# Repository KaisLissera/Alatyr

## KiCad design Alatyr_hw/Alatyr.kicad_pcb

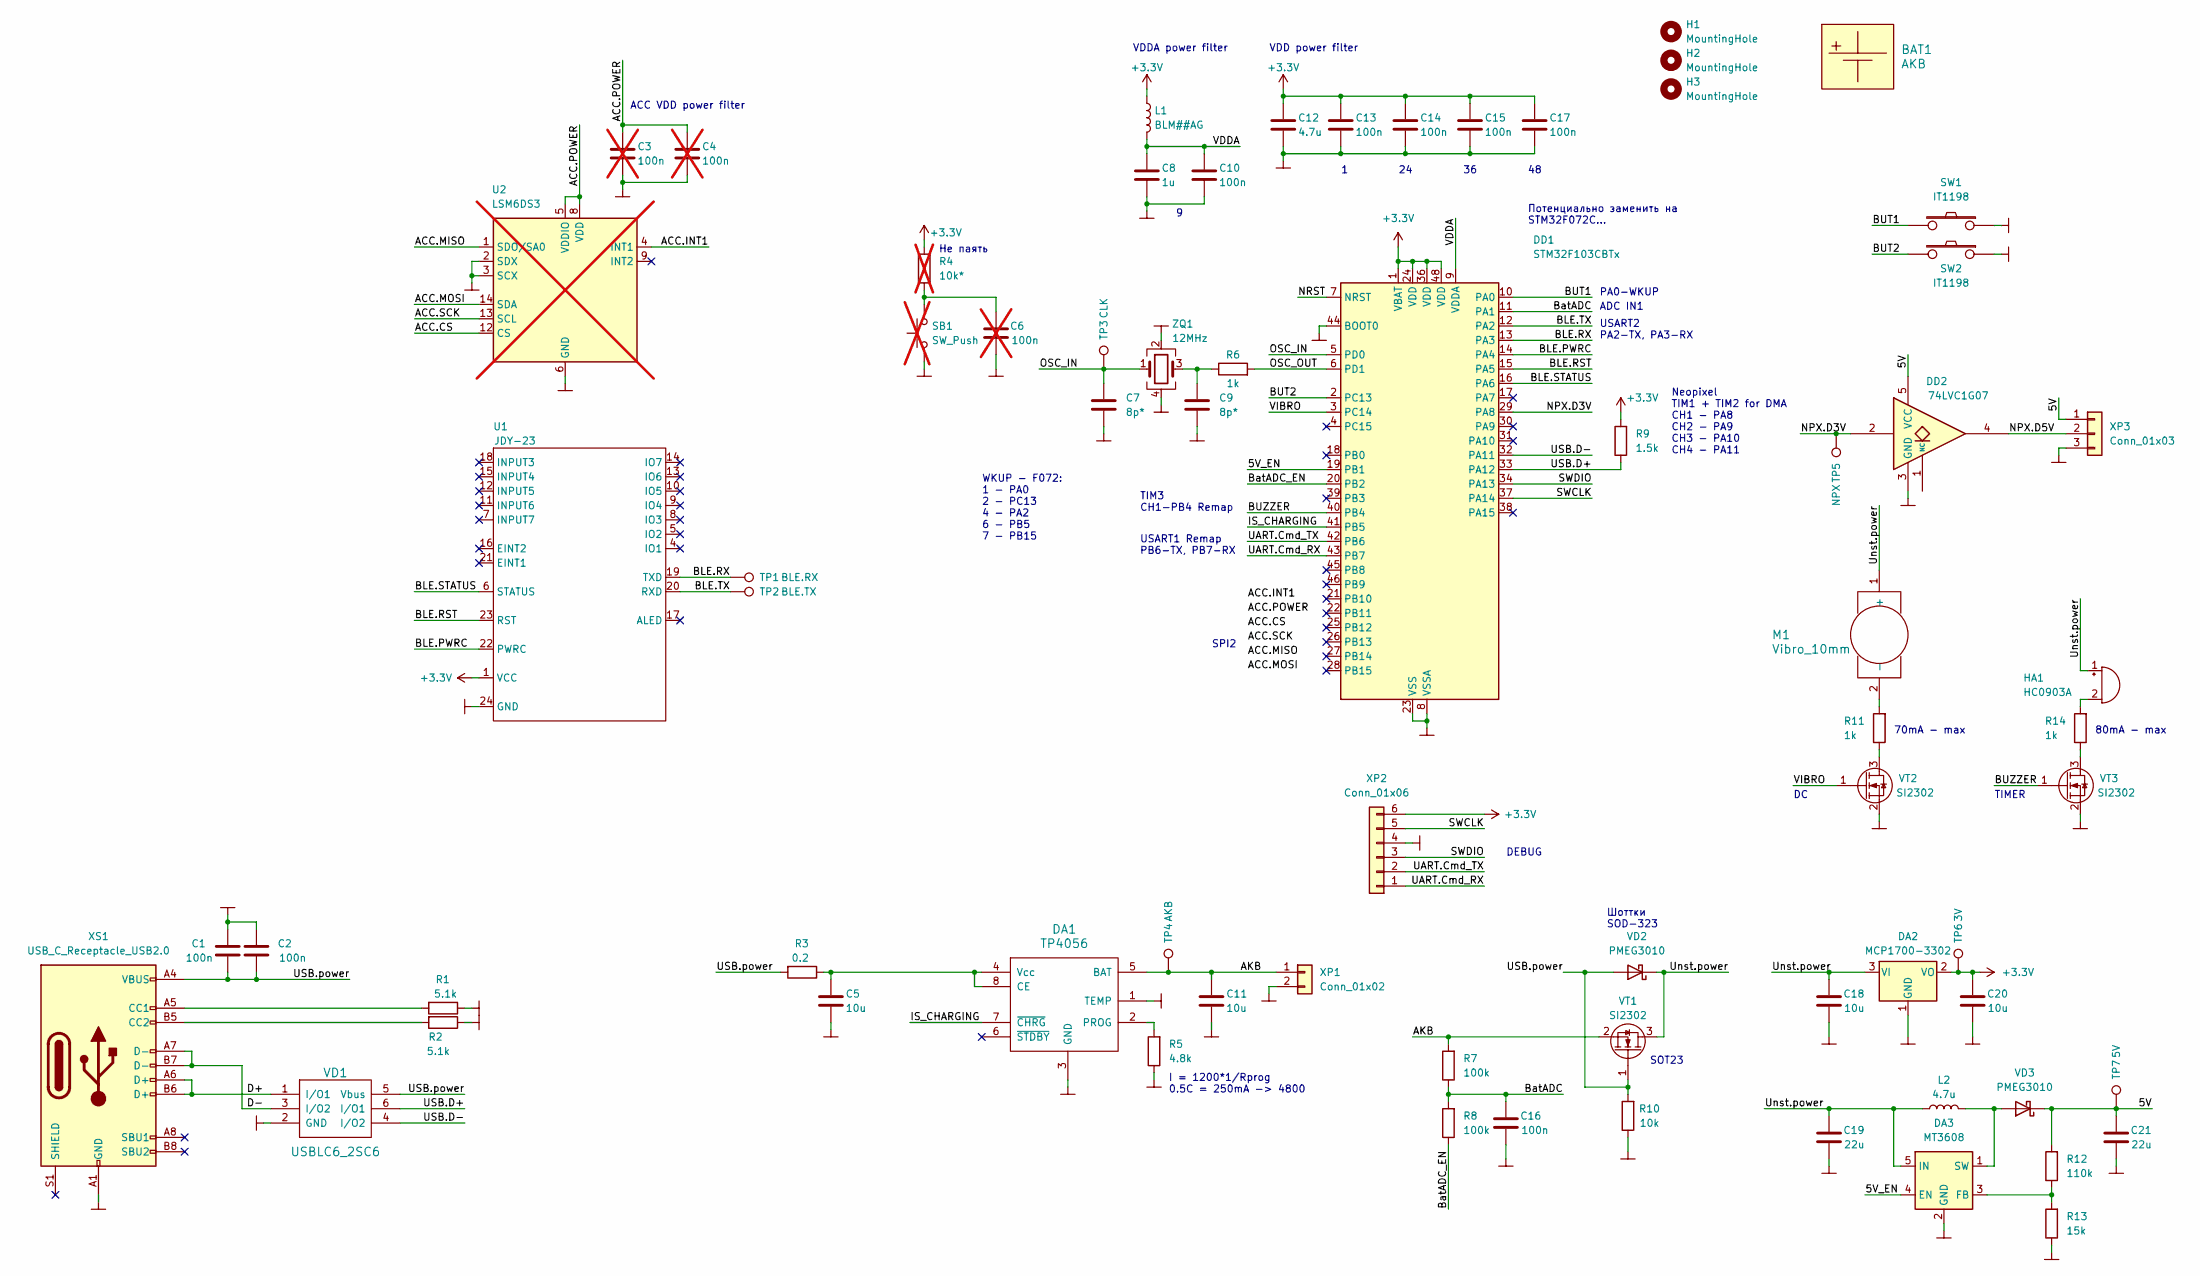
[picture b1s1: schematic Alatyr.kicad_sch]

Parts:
BAT1: AKB; AKB_05x30x40
C1, C2, C10, C13, C14, C15, C16, C17: 100n; C_0603_1608Metric_Pad1.08x0.95mm_HandSolder
C3, C4, C6: 100n; C_0603_1608Metric_Pad1.08x0.95mm_HandSolder; not fitted
C5, C11, C18, C20: 10u; C_0603_1608Metric_Pad1.08x0.95mm_HandSolder
C7, C9: 8p*; C_0603_1608Metric_Pad1.08x0.95mm_HandSolder
C8: 1u; C_0603_1608Metric_Pad1.08x0.95mm_HandSolder
C12: 4.7u; C_0603_1608Metric_Pad1.08x0.95mm_HandSolder
C19, C21: 22u; C_0603_1608Metric_Pad1.08x0.95mm_HandSolder
DA1: TP4056; SO-8_3.9x4.9mm_P1.27mm
DA2: MCP1700-3302; SOT-23-3
DA3: MT3608; SOT-23-6
DD1: STM32F103CBTx; LQFP-48_7x7mm_P0.5mm
DD2: 74LVC1G07; SOT-23-5
H1, H2, H3: MountingHole; MountingHole_2.5mm
HA1: HC0903A; MagneticBuzzer_CUI_CST-931RP-A
L1: BLM##AG; L_0603_1608Metric_Pad1.05x0.95mm_HandSolder
L2: 4.7u; L_0603_1608Metric_Pad1.05x0.95mm_HandSolder
M1: Vibro_10mm; Double_smd_solder
R1, R2: 5.1k; R_0603_1608Metric_Pad0.98x0.95mm_HandSolder
R3: 0.2; R_0603_1608Metric_Pad0.98x0.95mm_HandSolder
R4: 10k*; R_0603_1608Metric_Pad0.98x0.95mm_HandSolder; not fitted
R5: 4.8k; R_0603_1608Metric_Pad0.98x0.95mm_HandSolder
R6, R11, R14: 1k; R_0603_1608Metric_Pad0.98x0.95mm_HandSolder
R7, R8: 100k; R_0603_1608Metric_Pad0.98x0.95mm_HandSolder
R9: 1.5k; R_0603_1608Metric_Pad0.98x0.95mm_HandSolder
R10: 10k; R_0603_1608Metric_Pad0.98x0.95mm_HandSolder
R12: 110k; R_0603_1608Metric_Pad0.98x0.95mm_HandSolder
R13: 15k; R_0603_1608Metric_Pad0.98x0.95mm_HandSolder
SB1: SW_Push; SW_PUSH_6mm; not fitted
SW1, SW2: IT1198; BTN_IT1198
TP1: BLE.RX; TestPoint_Pad_D1.0mm
TP2: BLE.TX; TestPoint_Pad_D1.0mm
TP3: CLK; TestPoint_Pad_D1.0mm
TP4: AKB; TestPoint_Pad_D1.0mm
TP5: NPX; TestPoint_Pad_D1.0mm
TP6: 3V; TestPoint_Pad_D1.0mm
TP7: 5V; TestPoint_Pad_D1.0mm
U1: JDY-23; JDY-23_BLE_module
U2: LSM6DS3; LGA-14_3x2.5mm_P0.5mm_LayoutBorder3x4y; not fitted
VD1: USBLC6_2SC6; SOT-23-6
VD2, VD3: PMEG3010; D_SOD-323_HandSoldering
VT1, VT2, VT3: SI2302; SOT-23-3
XP1: Conn_01x02; PinHeader_1x02_P2.54mm_Vertical
XP2: Conn_01x06; PinHeader_1x06_P2.54mm_Vertical
XP3: Conn_01x03; PinHeader_1x03_P2.54mm_Vertical
XS1: USB_C_Receptacle_USB2.0; USB_C_Receptacle_XKB_U262-16XN-4BVC11
ZQ1: 12MHz; Crystal_SMD_3225-4Pin_3.2x2.5mm_HandSoldering

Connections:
+3V3: C12.1, C13.1, C14.1, C15.1, C17.1, C20.2, DA2.2 (VO), DD1.1 (VBAT), DD1.24 (VDD), DD1.36 (VDD), DD1.48 (VDD), L1.1, R9.2, TP6.1, U1.1 (VCC), XP2.6
/5V: C21.2, DD2.5 (VCC), R12.2, TP7.1, VD3.1 (K), XP3.1
/5V_EN: DA3.4 (EN), DD1.19 (PB1)
/AKB: C11.1, DA1.5 (BAT), R7.2, TP4.1, VT1.2 (S), XP1.1
/BLE.PWRC: DD1.14 (PA4), U1.22 (PWRC)
/BLE.RST: DD1.15 (PA5), U1.23 (RST)
/BLE.RX: DD1.13 (PA3), TP1.1, U1.19 (TXD)
/BLE.STATUS: DD1.16 (PA6), U1.6 (STATUS)
/BLE.TX: DD1.12 (PA2), TP2.1, U1.20 (RXD)
/BUT1: DD1.10 (PA0), SW1.2
/BUT2: DD1.2 (PC13), SW2.2
/BUZZER: DD1.40 (PB4), VT3.1 (G)
/BatADC: C16.2, DD1.11 (PA1), R7.1, R8.2
/BatADC_EN: DD1.20 (PB2), R8.1
/D+: VD1.1 (I/O1), XS1.A6 (D+), XS1.B6 (D+)
/D-: VD1.3 (I/O2), XS1.A7 (D-), XS1.B7 (D-)
/IS_CHARGING: DA1.7 (~CHRG), DD1.41 (PB5)
/NPX.D3V: DD1.29 (PA8), DD2.2, TP5.1
/NPX.D5V: DD2.4, XP3.2
/NRST: DD1.7 (NRST)
/OSC_IN: C7.1, DD1.5 (PD0), TP3.1, ZQ1.1
/OSC_OUT: DD1.6 (PD1), R6.2
/SWCLK: DD1.37 (PA14), XP2.5
/SWDIO: DD1.34 (PA13), XP2.3
/UART.Cmd_RX: DD1.43 (PB7), XP2.1
/UART.Cmd_TX: DD1.42 (PB6), XP2.2
/USB.D+: DD1.33 (PA12), R9.1, VD1.6 (I/O1)
/USB.D-: DD1.32 (PA11), VD1.4 (I/O2)
/USB.power: C1.1, C2.1, R3.2, R10.2, VD1.5 (Vbus), VD2.2 (A), VT1.1 (G), XS1.A4 (VBUS), XS1.A9 (VBUS), XS1.B4 (VBUS), XS1.B9 (VBUS)
/Unst.power: C18.2, C19.2, DA2.3 (VI), DA3.5 (IN), HA1.1 (-), L2.1, M1.1 (+), VD2.1 (K), VT1.3 (D)
/VDDA: C8.1, C10.1, DD1.9 (VDDA), L1.2
/VIBRO: DD1.3 (PC14), VT2.1 (G)
GND: C1.2, C2.2, C5.2, C7.2, C8.2, C9.2, C10.2, C11.2, C12.2, C13.2, C14.2, C15.2, C16.1, C17.2, C18.1, C19.1, C20.1, C21.1, DA1.1 (TEMP), DA1.3 (GND), DA2.1 (GND), DA3.2 (GND), DD1.8 (VSSA), DD1.23 (VSS), DD1.35 (VSS), DD1.44 (BOOT0), DD1.47 (VSS), DD2.3 (GND), R1.1, R2.1, R5.1, R10.1, R13.1, SW1.1, SW2.1, U1.24 (GND), VD1.2 (GND), VT2.2 (S), VT3.2 (S), XP1.2, XP2.4, XP3.3, XS1.A1 (GND), XS1.A12 (GND), XS1.B1 (GND), XS1.B12 (GND), ZQ1.2, ZQ1.4
unnamed: C3.1, C4.1, U2.5 (VDDIO), U2.8 (VDD)
unnamed: C6.2, R4.1, SB1.2
unnamed: C9.1, R6.1, ZQ1.3
unnamed: C5.1, DA1.4 (Vcc), DA1.8 (CE), R3.1
unnamed: DA1.2 (PROG), R5.2
unnamed: DA3.3 (FB), R12.1, R13.2
unnamed: DA3.1 (SW), L2.2, VD3.2 (A)
unnamed: HA1.2 (+), R14.2
unnamed: M1.2 (-), R11.2
unnamed: R11.1, VT2.3 (D)
unnamed: R14.1, VT3.3 (D)
unnamed: R1.2, XS1.A5 (CC1)
unnamed: R2.2, XS1.B5 (CC2)

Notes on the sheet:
WKUP - F072: 1 - PA0 2 - PC13 4 - PA2 6 - PB5 7 - PB15
80mA - max
PA0-WKUP
70mA - max
I = 1200*1/Rprog 0.5C = 250mA -> 4800
VDD power filter
SOT23
VDDA power filter
Не паять
USART2 PA2-TX, PA3-RX
Neopixel TIM1 + TIM2 for DMA CH1 - PA8 CH2 - PA9 CH3 - PA10 CH4 - PA11
TIMER
ACC VDD power filter
ADC IN1
DEBUG
SPI2
Шоттки SOD-323
USART1 Remap PB6-TX, PB7-RX
TIM3 CH1-PB4 Remap
Потенциально заменить на STM32F072C...

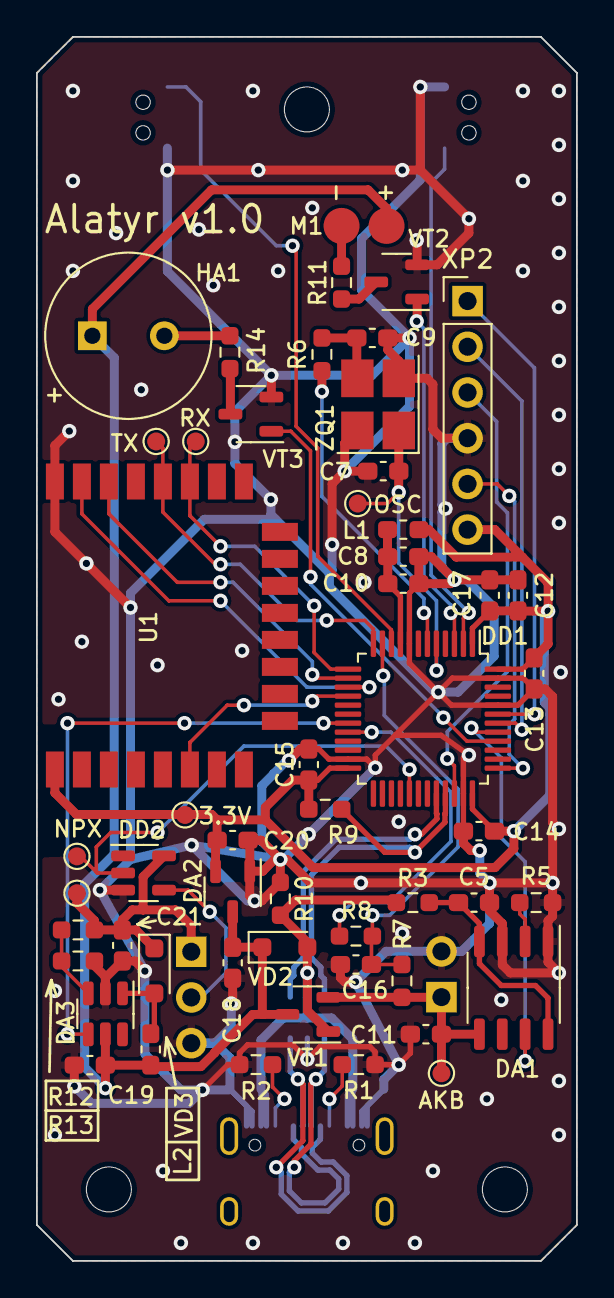
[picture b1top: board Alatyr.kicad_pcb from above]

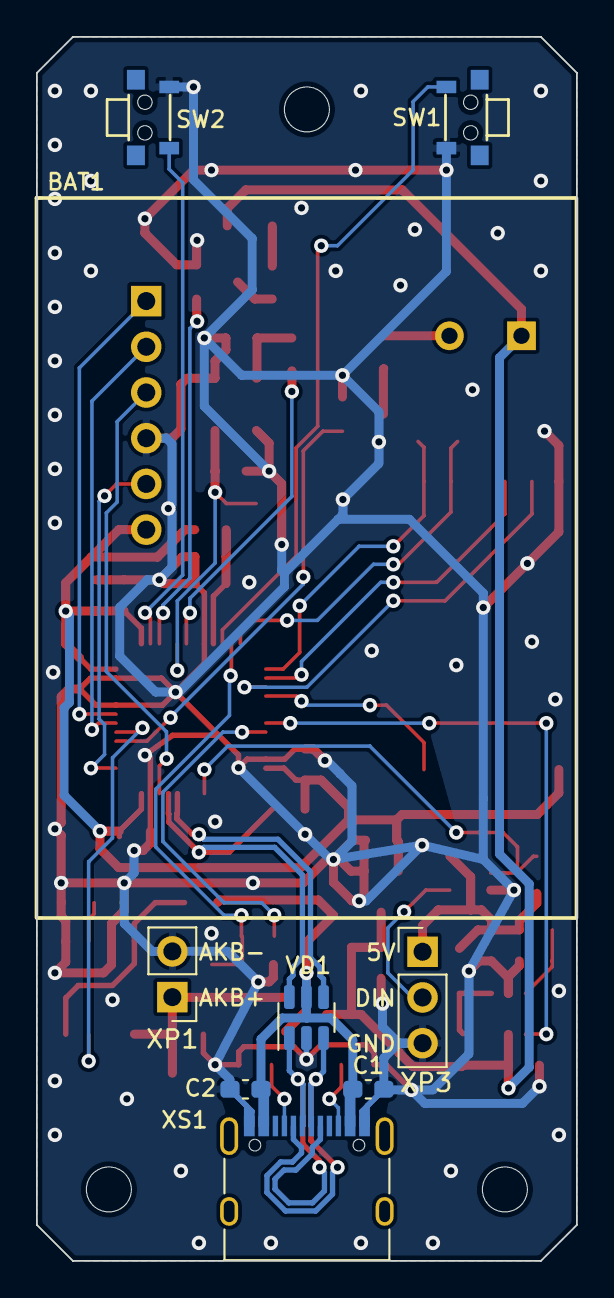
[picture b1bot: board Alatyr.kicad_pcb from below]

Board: 2 copper layers, 30.0 x 68.0 mm, 65 parts (9 on the bottom side), 43 nets.

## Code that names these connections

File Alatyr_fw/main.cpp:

/*
 * main.cpp
 *
 *  Created on: Mar 12, 2024
 *      Author: KONSTANTIN
 */

#include <stdint.h>
#include <interface_F103.h>
#include <rcc_F103.h>
#include <gpio_F103.h>
#include <tim_F103.h>
#include <neopixel.h>

#include <stm32f1xx.h>

#include <FreeRTOS.h>
#include <task.h>

//RTOS tasks declarations and priorities
/////////////////////////////////////////////////////////////////////
#define DEFAULT_TASK_PRIORITY 1

#define UART_IRQ_PRIORITY configSTM_MAX_SYSCALL_INTERRUPT_PRIORITY
#define DMA_IRQ_PRIORITY configSTM_MAX_SYSCALL_INTERRUPT_PRIORITY

TaskHandle_t NeopixelTaskHandle;
void NeopixelTask(void *pvParametrs);

TaskHandle_t BleTaskHandle;
void BleTask(void *pvParametrs);

TaskHandle_t ButtonTaskHandle;
void ButtonTask(void *pvParametrs);

// Uart shell for debug
Uart_t CmdUart; // UART1
DmaChannel_t DmaCh4 = {.Channel = DMA1_Channel4, .Number = 4, .Irq = DMA1_Channel4_IRQn};
uint8_t CmdTxBuffer[128];
DmaTx_t CmdTxDma(&DmaCh4, CmdTxBuffer, 128);
Cli_t CmdCli(&CmdTxDma, &CmdUart);

// Bluetooth
Uart_t BleUart; // UART2
DmaChannel_t DmaCh7 = {.Channel = DMA1_Channel7, .Number = 7, .Irq = DMA1_Channel7_IRQn};
uint8_t BleTxBuffer[128];
DmaTx_t BleTxDma(&DmaCh7, BleTxBuffer, 128);
DmaChannel_t DmaCh6 = {.Channel = DMA1_Channel6, .Number = 6, .Irq = DMA1_Channel6_IRQn};
uint8_t BleRxBuffer[128];
DmaRx_t BleRxDma(&DmaCh6, BleRxBuffer, 128);
Cli_t BleCli(&BleTxDma, &BleRxDma);

// Neopixel
#define NEOPIXEL_LENGTH 6
DmaChannel_t DmaCh5 = {.Channel = DMA1_Channel5, .Number = 5, .Irq = DMA1_Channel5_IRQn};
uint8_t NeopixelBuffer[24*NEOPIXEL_LENGTH];
Neopixel_t LedStrip(TIM1, 1, &DmaCh5, NeopixelBuffer, NEOPIXEL_LENGTH);

Button_t Button1(PA0, PullUp);
Button_t Button2(PC13, PullUp);

extern "C" {
	void DMA1_Channel4_IRQHandler(){
		CmdTxDma.IrqHandler();
	}
	void DMA1_Channel7_IRQHandler(){
		BleTxDma.IrqHandler();
	}
	void DMA1_Channel5_IRQHandler(){
		LedStrip.IrqHandler();
	}
}

//RTOS tasks
/////////////////////////////////////////////////////////////////////
#define NEOPIXEL_POLL 100
uint8_t NpxBrigthness = 15;
void NeopixelTask(void *pvParameters){
	uint32_t counter = 0;
	while(1){
		for(uint8_t i = 0; i < NEOPIXEL_LENGTH; i++)
			LedStrip.WriteLedColor(i, MakeHexGrbColor((counter + i) & 255, NpxBrigthness));
		LedStrip.Update();
		counter++;
		vTaskDelay(pdMS_TO_TICKS(NEOPIXEL_POLL));
	}
}

#define BLE_ANSWER_DELAY 100
void SendCommandAndWaitAnswer(const char* command){
	gpio::DeactivatePin(PA4);
	BleCli.Printf("%s\r\n", command);
	CmdCli.Printf("[BLE] %s\r\n", command);
	vTaskDelay(pdMS_TO_TICKS(100));
	CmdCli.Printf("%s\r\n",BleCli.ReadLine());
	gpio::ActivatePin(PA4);
}

uint8_t stringCompare(const char* str1, const char* str2){
	uint32_t ptr = 0;
	while((str1[ptr] != '\0') or (str2[ptr] != '\0')){
		if(str1[ptr] != str2[ptr])
			return 0;
		ptr++;
	}
	return 1;
}

uint32_t stringToInt(const char* str1){
	uint32_t ptr = 0;
	uint32_t number = 0;
	while(str1[ptr] != '\0'){
		if((str1[ptr] >= '0') and (str1[ptr] <= '9')){
			number = number*10 + (str1[ptr] - '0');
			ptr++;
		}else
				return 0;
	}
	return number;
}

void BleTask(void *pvParameters){
	char* text = NULL;

	SendCommandAndWaitAnswer("AT+VER");
	SendCommandAndWaitAnswer("AT+MAC");
	SendCommandAndWaitAnswer("AT+NAMEGenshinVision");
	SendCommandAndWaitAnswer("AT+NAME");

	while(1){
		text = BleCli.Read();
		if(text != NULL){
			if(stringCompare(text, "reset"))
				NVIC_SystemReset();
			else if(stringCompare(text, "brightness")){
				text = BleCli.Read();
				NpxBrigthness = stringToInt(text);
				BleCli.Printf("Neopixel brihtness: %d\r\n", NpxBrigthness);
			}else if(stringCompare(text, "sleep")){
				power::EnableWakeup1();
				power::EnterStandby();
			}else if(stringCompare(text, "npxpower")){
				text = BleCli.Read();
				if(stringToInt(text) == 0){
					BleCli.Printf("Npx power disabled\r\n");
					gpio::DeactivatePin(PB1);
				}else{
					BleCli.Printf("Npx power enabled\r\n");
					gpio::ActivatePin(PB1);
				}
			}else
				BleCli.Printf("Unknown command: %s\r\n", text);
		}
		vTaskDelay(pdMS_TO_TICKS(500));
	}
}

#define BUTTON_POLL_DELAY 200
void ButtonTask(void *pvParameters){
	while(1){
		ButtonState_t button1 = Button1.CheckState();
		ButtonState_t button2 = Button2.CheckState();

		switch(button1){
		case Pressed:
			CmdCli.Printf("Button 1 pressed\n\r");
			break;
		case HoldDown:
			CmdCli.Printf("Button 1 hold down\n\r");
			break;
		case Idle:
			break;
		case Released:
			CmdCli.Printf("Button 1 released\n\r");
			break;
		}

		switch(button2){
		case Pressed:
			CmdCli.Printf("Button 2 pressed\n\r");
			break;
		case HoldDown:
			CmdCli.Printf("Button 2 hold down\n\r");
			break;
		case Idle:
			break;
		case Released:
			CmdCli.Printf("Button 2 released\n\r");
			break;
		}

		vTaskDelay(pdMS_TO_TICKS(BUTTON_POLL_DELAY));
	}
}

int main(){
	flash::SetFlashPrefetchAndLatency(1);
	rcc::EnableHSI8();
	rcc::SetupPLL(pllSrcHsiDiv2, 8);
	rcc::EnablePLL();
	rcc::SwitchSysClk(sysClkPll);

	//Enable peripheral clock
	rcc::EnableClkAHB(RCC_AHBENR_DMA1EN);

	rcc::EnableClkAPB1(RCC_APB1ENR_USART2EN);

	rcc::EnableClkAPB2(RCC_APB2ENR_TIM1EN);
	rcc::EnableClkAPB2(RCC_APB2ENR_AFIOEN);
	rcc::EnableClkAPB2(RCC_APB2ENR_IOPAEN);
	rcc::EnableClkAPB2(RCC_APB2ENR_IOPBEN);
	rcc::EnableClkAPB2(RCC_APB2ENR_IOPCEN);
	rcc::EnableClkAPB2(RCC_APB2ENR_USART1EN);

	uint32_t currentSystemClock = rcc::GetCurrentSystemClock();
	uint32_t currentAhbClock = rcc::GetCurrentAHBClock(currentSystemClock);
	uint32_t currentApb1Clock = rcc::GetCurrentAPB1Clock(currentAhbClock);
	uint32_t currentApb2Clock = rcc::GetCurrentAPB2Clock(currentAhbClock);

	//USART1
	gpio::Afio1Remap(AFIO_MAPR_USART1_REMAP);
	gpio::SetupPin(PB6, AfOutput10MHzPushPull); // USART1 TX afer remap
	gpio::SetupPin(PB7, InputWithPull, PullUp); // USART1 RX after remap
	CmdUart.Init(USART1, currentApb2Clock, 115200);
	CmdUart.EnableDmaRequest(USART_CR3_DMAT);
	CmdUart.Enable();

	//USART1 DMA for command line
	CmdTxDma.Init((uint32_t)&USART1->DR);
//	DmaRxUart1.Init((uint32_t)&USART1->DR);
//	DmaRxUart1.Start();

	//USART2 for BLE
	gpio::SetupPin(PA2, AfOutput10MHzPushPull); // USART2 TX
	gpio::SetupPin(PA3, InputWithPull, PullUp); // USART2 RX
	BleUart.Init(USART2, currentApb1Clock, 9600);
	BleUart.EnableDmaRequest(USART_CR3_DMAT|USART_CR3_DMAR);
	BleUart.Enable();

	//DMA for BLE
	BleTxDma.Init((uint32_t)&USART2->DR);
	BleRxDma.Init((uint32_t)&USART2->DR);
	BleRxDma.Start();

	gpio::SetupPin(PA4, Output10MHzPushPull);
	gpio::SetupPin(PA5, Output10MHzPushPull);
	gpio::SetupPin(PA6, InputFloating);
	gpio::ActivatePin(PA4); // BLE PWRC
	gpio::ActivatePin(PA5); // BLE RST

	//Neopixel
	gpio::SetupPin(PB1, Output10MHzPushPull);
	gpio::ActivatePin(PB1); // 5V DC-DC enable
	gpio::SetupPin(PA8, AfOutput10MHzPushPull); // TIM1 channel 1
	LedStrip.Init(rcc::GetCurrentTimersClock(currentApb2Clock), 0);
	LedStrip.Clear();

	// Buttons
	Button1.Init();
	Button2.Init();

	CmdCli.Printf("[SYS] Clock %d\n\r",currentSystemClock);

	xTaskCreate(&NeopixelTask, "NPX", 512, NULL,
			DEFAULT_TASK_PRIORITY, &NeopixelTaskHandle);
	xTaskCreate(&BleTask, "BLE", 512, NULL,
			DEFAULT_TASK_PRIORITY, &BleTaskHandle);
	xTaskCreate(&ButtonTask, "BTN", 512, NULL,
			DEFAULT_TASK_PRIORITY, &ButtonTaskHandle);

	CmdCli.Printf("[SYS] Starting sheduler\n\r");
	vTaskStartScheduler();
	while(1);
}

//Main and FreeRTOS hooks
/////////////////////////////////////////////////////////////////////
void vApplicationMallocFailedHook(){
	CmdCli.Printf("[ERR] Malloc failed\n\r");
}

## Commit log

2023-11-25 PCB wired, small cover fixes
2024-03-12 Start writing firmware
2024-03-16 Neopixel works
2024-03-17 refactoring
2024-03-21 bluetooth working, add FreeRTOS
2024-04-05 new cover, bluethooth commands
